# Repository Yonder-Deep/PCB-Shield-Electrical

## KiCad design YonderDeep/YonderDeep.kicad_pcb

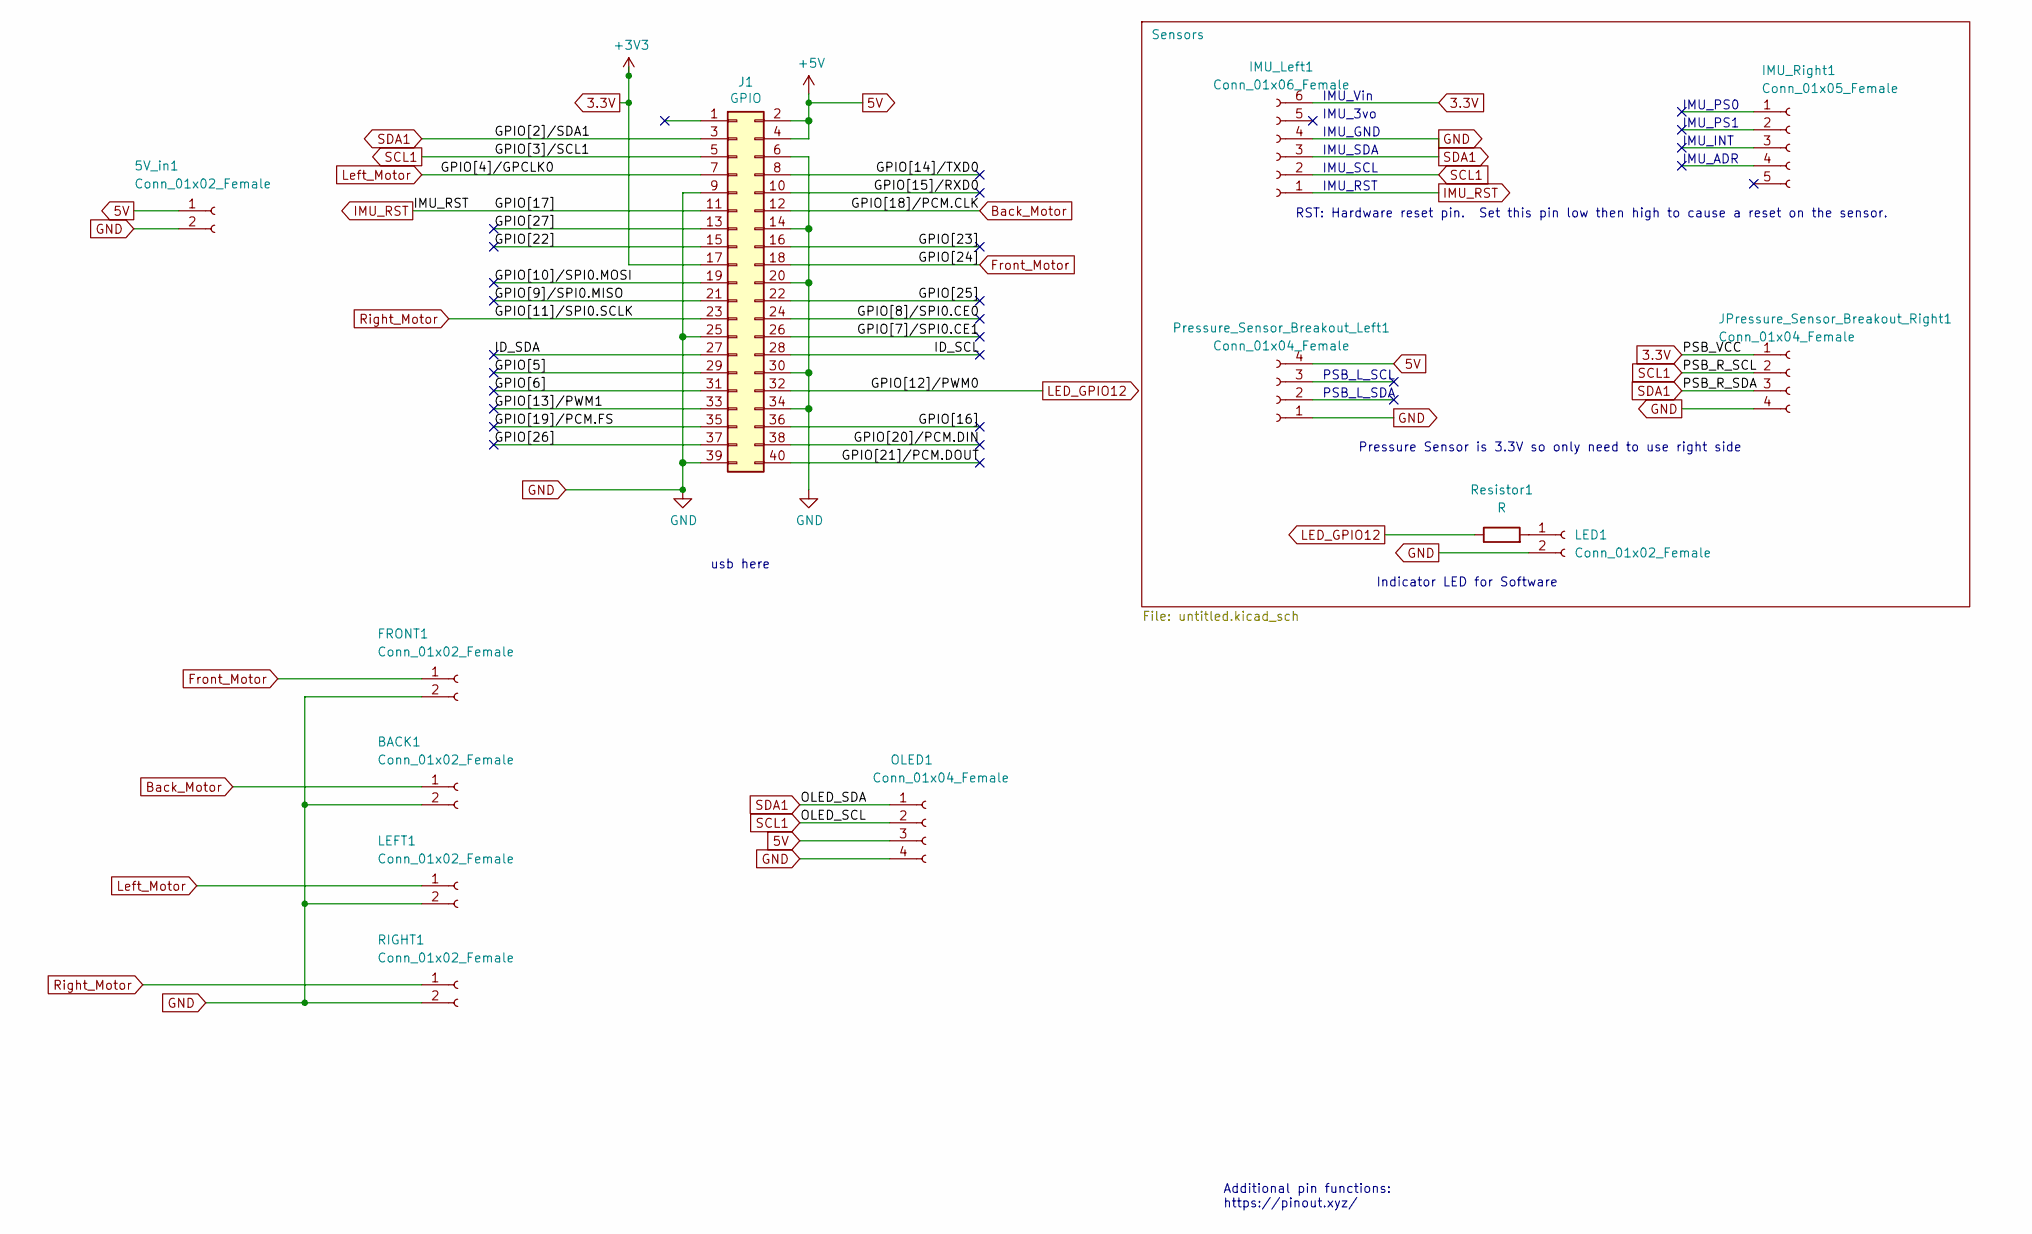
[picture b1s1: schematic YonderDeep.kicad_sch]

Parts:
5V_in1: Conn_01x02_Female; TerminalBlock_MetzConnect_Type101_RT01602HBWC_1x02_P5.08mm_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
BACK1: Conn_01x02_Female; C_Rect_L7.0mm_W2.5mm_P5.00mm
FRONT1: Conn_01x02_Female; C_Rect_L7.0mm_W2.5mm_P5.00mm
IMU_Left1: Conn_01x06_Female; PinHeader_1x06_P2.54mm_Vertical
IMU_Right1: Conn_01x05_Female; PinHeader_1x05_P2.54mm_Vertical
J1: GPIO; PinSocket_2x20_P2.54mm_Vertical
JPressure_Sensor_Breakout_Right1: Conn_01x04_Female; PinHeader_1x04_P2.54mm_Vertical
LED1: Conn_01x02_Female; LED_D3.0mm
LEFT1: Conn_01x02_Female; C_Rect_L7.0mm_W2.5mm_P5.00mm
OLED1: Conn_01x04_Female; PinHeader_1x04_P2.54mm_Vertical
Pressure_Sensor_Breakout_Left1: Conn_01x04_Female; PinHeader_1x04_P2.54mm_Vertical
RIGHT1: Conn_01x02_Female; C_Rect_L7.0mm_W2.5mm_P5.00mm
Resistor1: R; R_Box_L8.4mm_W2.5mm_P5.08mm

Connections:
3.3V: IMU_Left1.6, J1.17, JPressure_Sensor_Breakout_Right1.1
5V: 5V_in1.1, J1.2, J1.4, OLED1.3, Pressure_Sensor_Breakout_Left1.4
/GPIO[5]: J1.29
/GPIO[6]: J1.31
/GPIO[7]/SPI0.CE1: J1.26
/GPIO[8]/SPI0.CE0: J1.24
/GPIO[9]/SPI0.MISO: J1.21
/GPIO[10]/SPI0.MOSI: J1.19
/GPIO[13]/PWM1: J1.33
/GPIO[14]/TXD0: J1.8
/GPIO[15]/RXD0: J1.10
/GPIO[16]: J1.36
/GPIO[19]/PCM.FS: J1.35
/GPIO[20]/PCM.DIN: J1.38
/GPIO[21]/PCM.DOUT: J1.40
/GPIO[22]: J1.15
/GPIO[23]: J1.16
/GPIO[25]: J1.22
/GPIO[26]: J1.37
/GPIO[27]: J1.13
/ID_SCL: J1.28
/ID_SDA: J1.27
Back_Motor: BACK1.1, J1.12
Front_Motor: FRONT1.1, J1.18
GND: 5V_in1.2, BACK1.2, FRONT1.2, IMU_Left1.4, J1.6, J1.9, J1.14, J1.20, J1.25, J1.30, J1.34, J1.39, JPressure_Sensor_Breakout_Right1.4, LED1.2, LEFT1.2, OLED1.4, Pressure_Sensor_Breakout_Left1.1, RIGHT1.2
IMU_RST: IMU_Left1.1, J1.11
LED_GPIO12: J1.32, Resistor1.1
Left_Motor: J1.7, LEFT1.1
unnamed: LED1.1, Resistor1.2
Right_Motor: J1.23, RIGHT1.1
SCL1: IMU_Left1.2, J1.5, JPressure_Sensor_Breakout_Right1.2, OLED1.2
SDA1: IMU_Left1.3, J1.3, JPressure_Sensor_Breakout_Right1.3, OLED1.1

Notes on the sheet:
IMU_PS0
Indicator LED for Software
IMU_RST
Additional pin functions: https://pinout.xyz/
PSB_L_SCL
usb here
IMU_GND
IMU_Vin
Pressure Sensor is 3.3V so only need to use right side
IMU_SCL
IMU_SDA
IMU_ADR
IMU_INT
PSB_L_SDA
IMU_3vo
IMU_PS1
RST: Hardware reset pin. Set this pin low then high to cause a reset on the sensor.

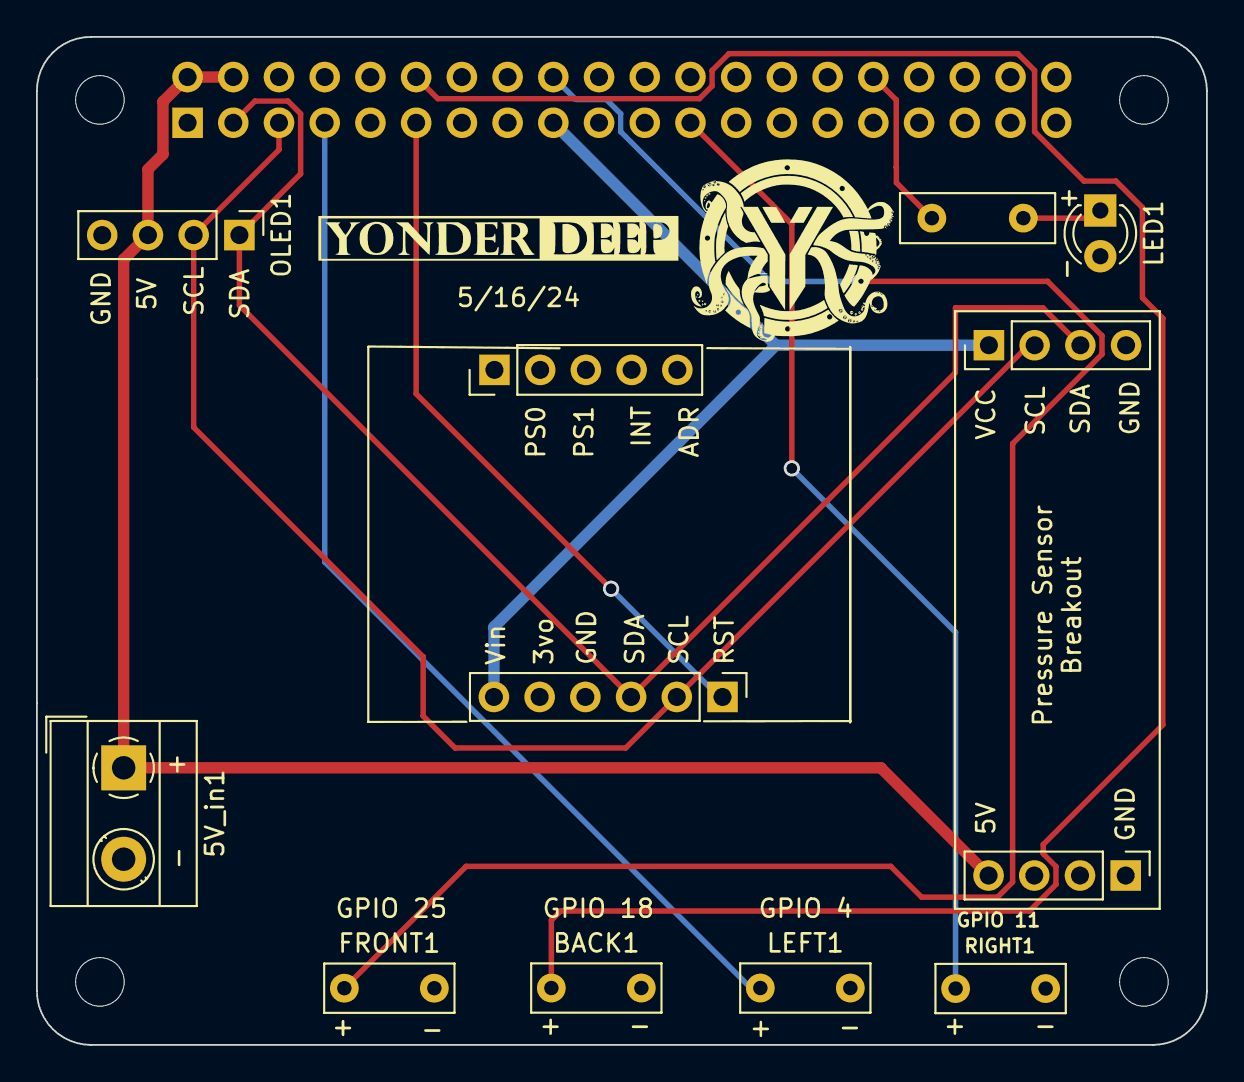
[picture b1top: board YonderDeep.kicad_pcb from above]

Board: 2 copper layers, 65.0 x 56.0 mm, 17 parts (1 on the bottom side), 12 nets.

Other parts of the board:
MH1, MH2, MH3, MH4: MountingHole_2.7mm_M2.5

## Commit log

2023-05-22 Need to add motor pins on rpi
    Schematic:
    1) Sensor pins: Pressure Sensor, IMU
    2) Shield 5_in
    Need:
    1) Motor ESC pins
    2) PCB through hole placements
2023-05-23 Working on PCB placement
2023-05-27 DRC no error
2023-05-27 small trace edit
2023-05-27 passes jlc gerber viewer
2023-05-27 Cleaned up files. Ready to order.
2023-05-28 LED Resistor added
2023-05-31 Added signature
2025-05-17 Update
    PCB update IMU pin footprint and new labels
